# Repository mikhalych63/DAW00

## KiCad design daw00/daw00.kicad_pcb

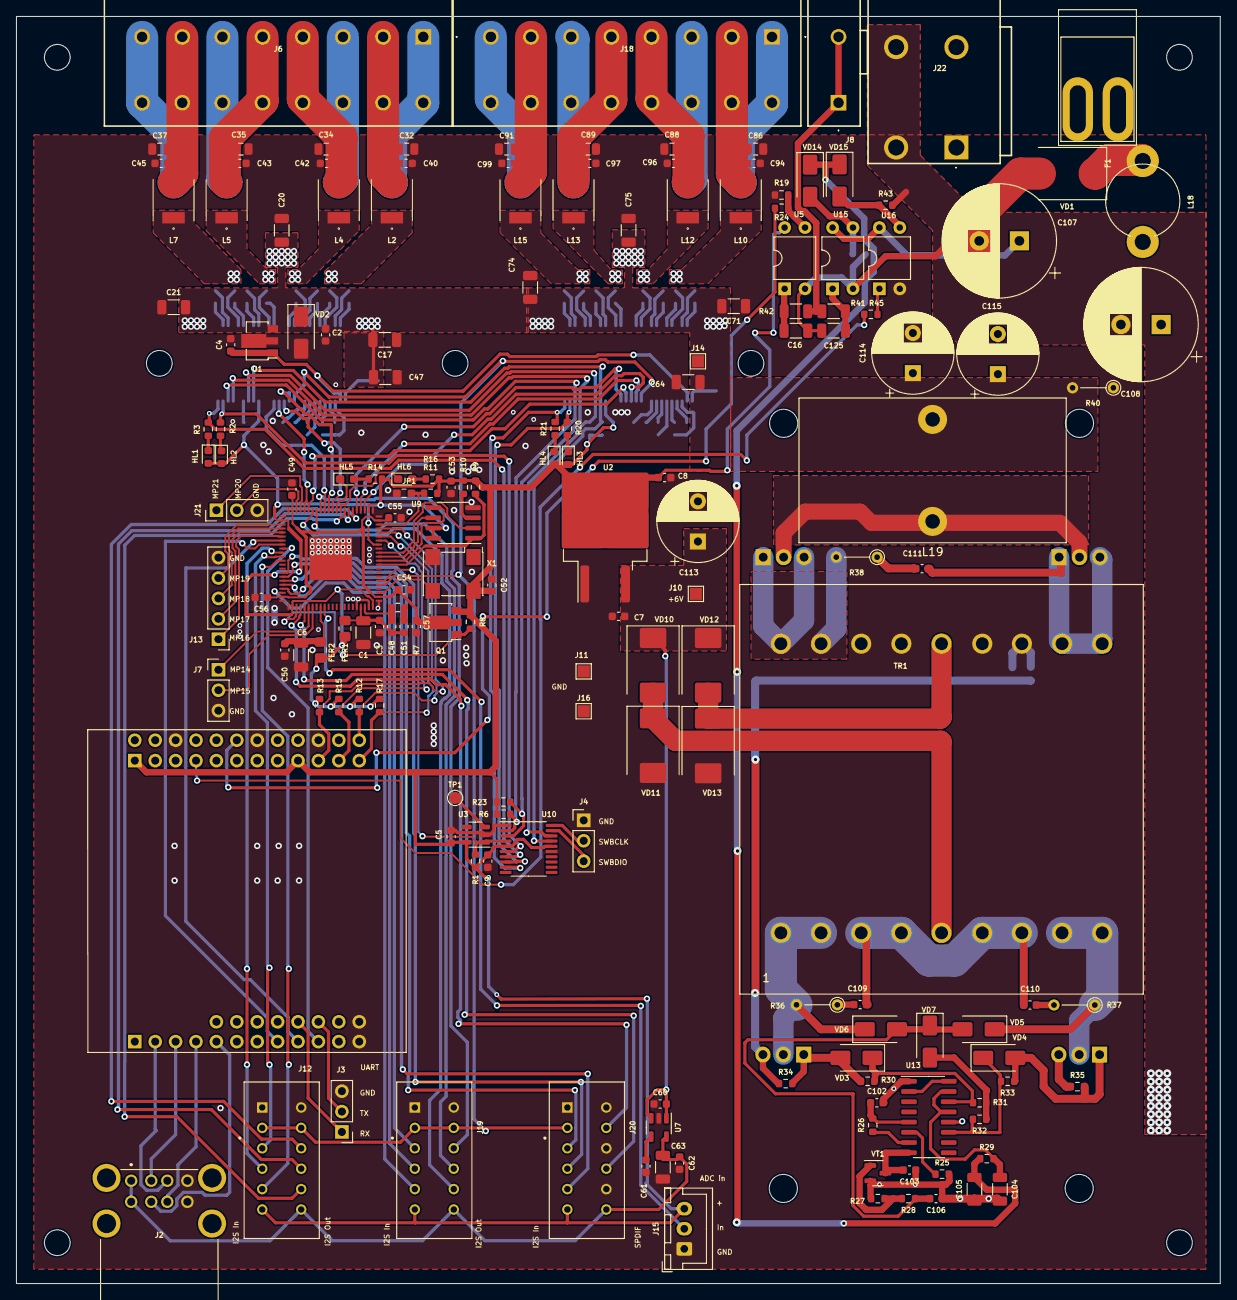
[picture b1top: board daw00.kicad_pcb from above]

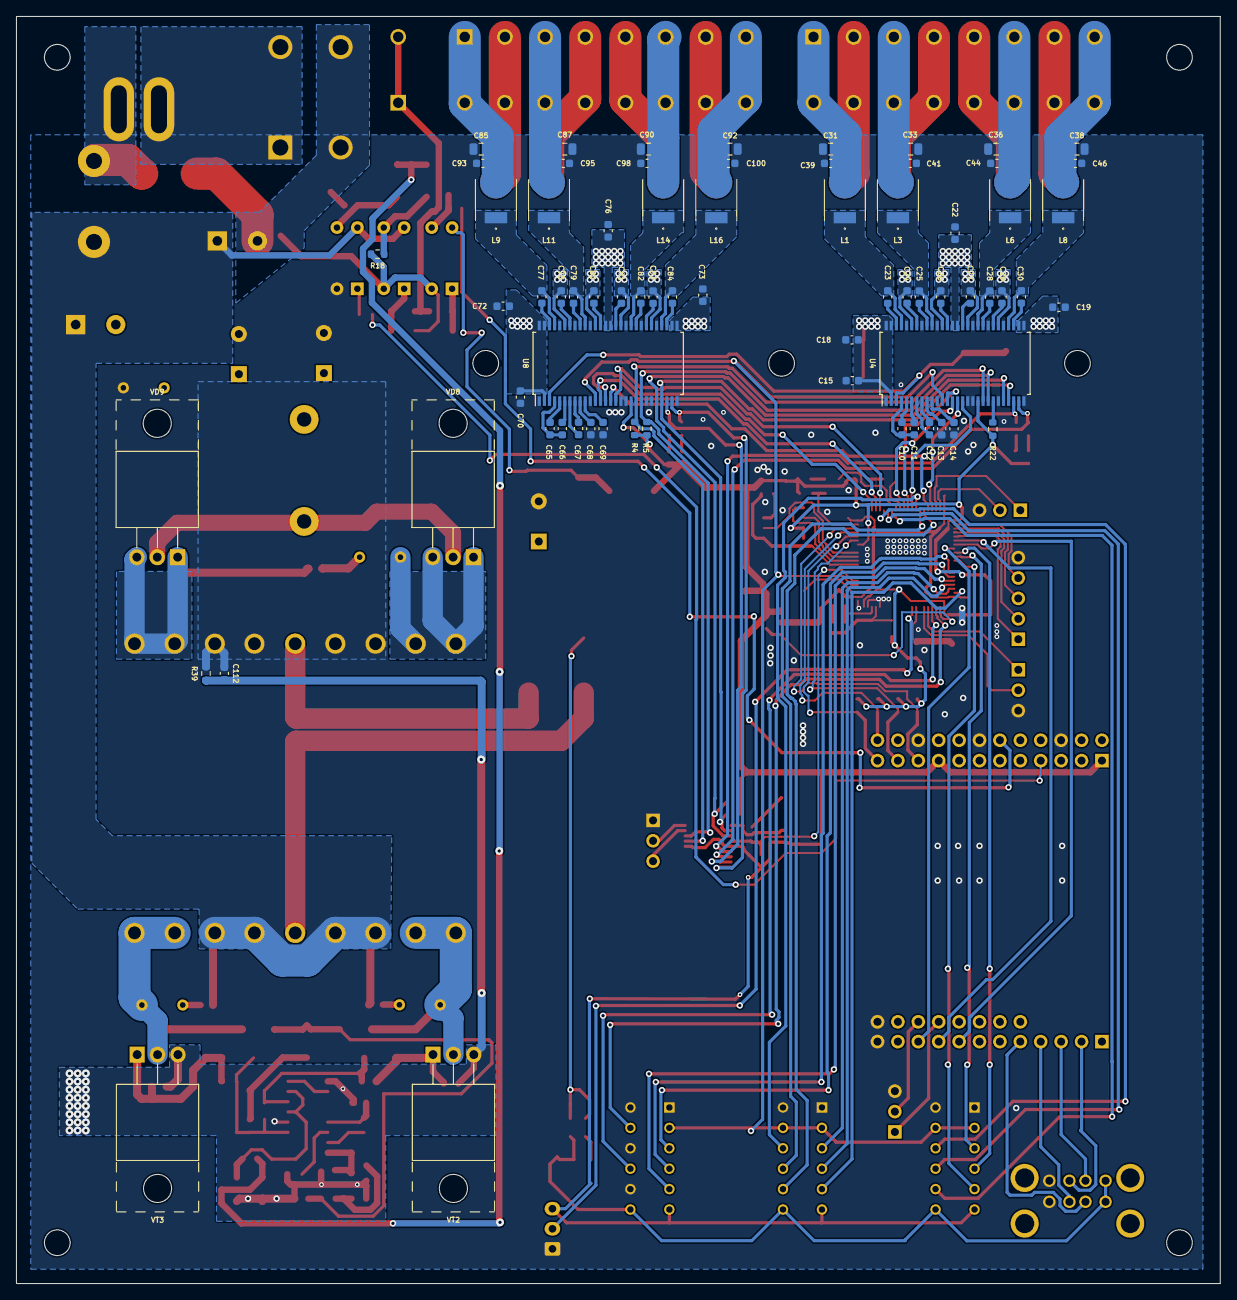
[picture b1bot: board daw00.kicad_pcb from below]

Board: 2 copper layers, 149.9 x 157.7 mm, 239 parts (70 on the bottom side), 188 nets.

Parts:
C1, C6, C16, C105, C125: CAP_10u0_50V_X7R_1206; C_1206_3216Metric
C2, C7: 0,33uF; C_0603_1608Metric
C3, C5, C50, C53, C54, C55, C56, C57, C112: CAP_100n_50V_X7R_0603; C_0603_1608Metric
C4, C8, C9, C15, C18, C19, C22, C60, C62, C70, C72, C73, C76: 100n; C_0603_1608Metric
C10, C11, C12, C13, C14, C23, C24, C25, C26, C27, C28, C29, C30, C65, C66, C67, C68, C69, C77, C78, C79, C80, C81, C82, C83, C84: 1,0uF; C_0603_1608Metric
C17, C20, C21, C47, C63, C64, C71, C74, C75: 10,0uF; C_1206_3216Metric
C31, C32, C33, C34, C35, C36, C37, C38, C85, C86, C87, C88, C89, C90, C91, C92: 1.0uF; C_0805_2012Metric
C39, C40, C41, C42, C43, C44, C45, C46, C61, C93, C94, C95, C96, C97, C98, C99, C100: 10n; C_0603_1608Metric
C48: CAP_150p_50V_C0G_0603; C_0603_1608Metric
C49, C103, C106: CAP_10n_50V_X7R_0603; C_0603_1608Metric
C51: CAP_5n6_50V_X7R_0603; C_0603_1608Metric
C52: CAP_10n_25V_X7R_0603; C_0603_1608Metric
C102, C111: CAP_1n_50V_X7R_0603; C_0603_1608Metric
C104: CAP_2u2_50V_X7R_1206; C_1206_3216Metric
C107, C108: 2200μ; CP_Radial_D14.0mm_P5.00mm
C109, C110: CAP_22n_50V_X7R_0603; C_0603_1608Metric
C113, C114, C115: 330μ; CP_Radial_D10.0mm_P5.00mm
F1: Fuse; Fuse_Blade_vertical
FER1, FER2: BLM21AG102SN1D; R_0805_2012Metric_Pad1.20x1.40mm_HandSolder
HL1, HL4: LED_SMD_0603_YELLOW; LED_0603_1608Metric
HL2, HL3: LED_SMD_0603_RED; LED_0603_1608Metric
HL5, HL6: LED_SMD_0603_BLUE; LED_0603_1608Metric_Pad1.05x0.95mm_HandSolder
J2: USB_A_Stacked; USB_A_STACKED
J3: UART; PinHeader_1x03_P2.54mm_Vertical
J4: SWD; PinHeader_1x03_P2.54mm_Vertical
J6, J18: DEGSON 2604 8x5; DEGSON_8x5
J7, J21: Conn_01x02_Male; PinHeader_1x03_P2.54mm_Vertical
J8: DEGSON 2604 1x5; DEGSON_1x5
J10: +6V; TestPoint_Pad_1.5x1.5mm
J11, J16: GND; TestPoint_Pad_1.5x1.5mm
J12, J19, J20: Conn_edge_2x6_2.54_Male; 2x6
J13: Conn_01x04_Male; PinHeader_1x05_P2.54mm_Vertical
J14: +24V; TestPoint_Pad_1.5x1.5mm
J15: Volume; JST_XH_B3B-XH-A_1x03_P2.50mm_Vertical
J22: KF206-7.5-2P; DEGSON_2x7.5
JP1: CON_JUMPER; R_0603_1608Metric_Pad0.98x0.95mm_HandSolder
L1, L2, L3, L4, L5, L6, L7, L8, L9, L10, L11, L12, L13, L14, L15, L16: 3.3uH; SPM5010-5020
L18: 5μ; L_Axial_L26.0mm_D9.0mm_P5.08mm_Vertical
L19: 25μ; L_Toroid_Vertical_L33.0mm_W17.8mm_P12.70mm_Pulse_KM-5
Q1: 2STF2360; SOT-89-3
R1, R6, R23: 10K; R_0603_1608Metric
R2, R3, R20, R21: 1K; R_0603_1608Metric
R4, R5, R22: 4k7; R_0603_1608Metric
R7: RES_4K3_1%_0.125W_Thick_0603; R_0603_1608Metric
R8: RES_1K0_1%_0.125W_Thick_0603; R_0603_1608Metric
R9, R10, R11, R12, R13, R15, R17: RES_10K0_1%_0.125W_Thick_0603; R_0603_1608Metric
R14, R16: RES_51R0_1%_0.125W_Thick_0603; R_0603_1608Metric
R18, R43: 4.7k; R_0603_1608Metric
R19: 10k; R_0603_1608Metric
R24, R31, R32, R34, R35, R39, R45: 1k; R_0603_1608Metric
R25: 15k; R_0603_1608Metric
R26: 150; R_0603_1608Metric
R27: 3k; R_0603_1608Metric
R28: 3,6k; R_0603_1608Metric
R29, R30, R33: 10; R_0603_1608Metric
R36, R37: 4.7; R_Axial_DIN0204_L3.6mm_D1.6mm_P5.08mm_Vertical
R38: 100; R_Axial_DIN0204_L3.6mm_D1.6mm_P5.08mm_Vertical
R40: 1.5k; R_Axial_DIN0204_L3.6mm_D1.6mm_P5.08mm_Vertical
R41, R42: 1.2k; R_1206_3216Metric
TP1: Reset; TestPoint_Pad_D1.5mm
TR1: TRANSF10; Transformer_ETD44_Horizontal
U1: L78L18_SOT89; SOT-89-3
U2: LD1086D2T33TR; TO-263-2
U3: TPS3828-33DBVT; SOT-23-5
U4, U8: TAS6424QDKQRQ1; SSOP-56_7.5x18.5mm_P0.635mm
U5, U15, U16: TLP627; DIP-4_W7.62mm
U6: ADAU1467WBCPZ300RL; LFCSP-88-1EP_10x10mm_P0.5mm_EP6.15x6.15mm
U7: LP2985-5.0; SOT-23-5
U9: 25AA1024-I/SM; SOIC-8_3.9x4.9mm_P1.27mm
U10: STM32F030F4Px; TSSOP-20_4.4x6.5mm_P0.65mm
U12: Nanopi NEO Air; Nanopi NEO
U13: SG3525; SOIC-16_3.9x9.9mm_P1.27mm
VD1, VD10, VD11, VD12, VD13: SS56; D_SMC
VD2: ES1D; D_SMA
VD3, VD4, VD5, VD14, VD15: 1N5819; D_SMA
VD6, VD7: 1N414E; D_SMA
VD8, VD9: MBR20100CT; TO-220-3_Horizontal_TabUp
VT1: BC846; SOT-23
VT2, VT3: IRF3205; TO-220-3_Horizontal_TabUp
X1: SG-8002CA 24.5760M-PCBL3; Oscillator_SMD_SeikoEpson_SG8002CA-4Pin_7.0x5.0mm

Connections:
+3V3: C5.2, C8.1, C9.2, C52.1, C53.1, FER1.2, FER2.2, HL1.2 (A), HL2.2 (A), HL3.2 (A), HL4.2 (A), J12.11, J15.3, J19.11, J20.11, Q1.3 (E), R1.1, R4.1, R5.1, R6.1, R8.2, R9.1, R10.1, R11.1, R12.1, R13.1, R14.1, R15.1, R16.1, R17.1, R22.2, R23.1, U2.2 (OUT), U3.5 (VDD), U4.19 (VDD), U5.4, U6.2 (IOVDD), U6.22 (IOVDD), U6.37 (IOVDD), U6.46 (IOVDD), U6.68 (IOVDD), U8.19 (VDD), U9.7 (~HOLD), U9.8 (VCC), U10.5 (VDDA), U10.16 (VDD), U12.1 (VDD_3.3V), U12.17 (VDD_3.3V), X1.4 (Vcc)
+5V: C62.2, C63.1, J2.1 (VBUS1), J2.5 (VBUS2), J12.12, J19.12, J20.12, U7.5 (VOUT)
+6V: C7.1, C60.2, C113.1, J10.1, U2.3 (IN), U7.1 (VIN), U7.3 (ON/~OFF), VD10.1 (K), VD12.1 (K)
+BATT: F1.1, J22.1
/Amplifier/AUXADC0: J15.2, U6.10 (AUXADC0)
/Amplifier/BCLKIN1: J12.7, U6.76 (BCLK_IN1)
/Amplifier/BCLKIN2: J20.7, U6.81 (BCLK_IN2)
/Amplifier/BCLKIN3: J19.7, U6.84 (BCLK_IN3)
/Amplifier/BCLKOUT0: U6.48 (BCLK_OUT0), U8.13 (SCLK)
/Amplifier/BCLKOUT1: J12.8, U6.51 (BCLK_OUT1)
/Amplifier/BCLKOUT2: U4.13 (SCLK), U6.56 (BCLK_OUT2)
/Amplifier/BCLKOUT3: J19.8, U6.59 (BCLK_OUT3)
/Amplifier/LRCKIN1: J12.5, U6.77 (LRCLK_IN1/MP11)
/Amplifier/LRCKIN2: J20.5, U6.82 (LRCLK_IN2/MP12)
/Amplifier/LRCKIN3: J19.5, U6.85 (LRCLK_IN3/MP13)
/Amplifier/LRCKOUT1: J12.6, U6.50 (LRCLK_OUT1/MP5)
/Amplifier/LRCKOUT3: J19.6, U6.58 (LRCLK_OUT3/MP9)
/Amplifier/LRCLKOUT0: U6.47 (LRCLK_OUT0/MP4), U8.14 (FSYNC)
/Amplifier/LRCLKOUT2: U4.14 (FSYNC), U6.55 (LRCLK_OUT2/MP8)
/Amplifier/SDATAIN1: J12.9, U6.78 (SDATA_IN1)
/Amplifier/SDATAIN2: J20.9, U6.83 (SDATA_IN2)
/Amplifier/SDATAIN3: J19.9, U6.86 (SDATA_IN3)
/Amplifier/SDATAOUT0: U6.49 (SDATA_OUT0), U8.16 (SDIN2)
/Amplifier/SDATAOUT1: J12.10, U6.52 (SDATA_OUT1)
/Amplifier/SDATAOUT1+: U6.61 (SDATAIO7/MP23), U8.15 (SDIN1)
/Amplifier/SDATAOUT2: U4.16 (SDIN2), U6.57 (SDATA_OUT2)
/Amplifier/SDATAOUT3: J19.10, U6.60 (SDATA_OUT3)
/Amplifier/SDATAOUT3+: U4.15 (SDIN1), U6.62 (SDATAIO6/MP22)
/Amplifier/SPDIFIN: J20.4, U6.4 (SPDIFIN)
/Amplifier/SPDIFOUT: J20.8, U6.5 (SPDIFOUT)
/Computer/SBWTCK: J4.2, U10.20 (PA14)
/Computer/SBWTDIO: J4.3, U10.19 (PA13)
ACC: J8.1, R41.2, R42.2
ACC_IN: R24.2, U12.12 (GPIO_A6)
BCLKIN0: U6.73 (BCLK_IN0), U12.39 (I2S0_BCK)
FAULT0: R21.2, U8.27 (FAULT), U10.9 (PA3)
FAULT1: R3.2, U4.27 (FAULT), U10.7 (PA1)
GND: C1.2, C2.2, C3.2, C4.2, C5.1, C6.2, C7.2, C8.2, C9.1, C13.2, C14.2, C15.1, C17.1, C18.1, C19.1, C20.2, C21.1, C22.2, C31.1, C32.2, C33.1, C34.2, C35.1, C36.2, C37.1, C38.2, C39.1, C40.2, C41.1, C42.2, C43.1, C44.2, C45.1, C46.2, C47.1, C49.2, C50.2, C52.2, C53.2, C54.2, C55.2, C56.2, C57.2, C60.1, C61.1, C62.1, C63.2, C64.1, C68.2, C69.2, C70.1, C71.1, C72.1, C73.1, C74.2, C75.1, C76.2, C85.1, C86.2, C87.1, C88.2, C89.1, C90.2, C91.1, C92.2, C93.1, C94.2, C95.1, C96.2, C97.1, C98.2, C99.1, C100.2, C112.1, C113.2, C114.2, C115.2, J2.4 (GND1), J2.8 (GND2), J3.3, J4.1, J7.3, J11.1, J12.1, J12.2, J13.5, J15.1, J16.1, J19.1, J19.2, J20.1, J20.2, J20.6, J20.10, J21.3, JP1.2, R19.2, R39.2, R40.1, TR1.6, TR1.7, U1.2 (GND), U2.1 (ADJ/GND), U3.2 (GND), U4.1 (GND), U4.11 (GND), U4.17 (GND), U4.18 (GND), U4.23 (I2C_ADDR1), U4.28 (GND), U4.33 (GND), U4.36 (GND), U4.39 (GND), U4.46 (GND), U4.49 (GND), U4.52 (GND), U6.1 (DGND), U6.8 (AGND), U6.18 (PGND), U6.21 (DGND), U6.23 (DGND), U6.29 (DGND), U6.36 (DGND), U6.44 (DGND), U6.45 (DGND), U6.66 (DGND), U6.67 (DGND), U6.88 (DGND), U6.89 (GND), U7.2 (GND), U8.1 (GND), U8.11 (GND), U8.17 (GND), U8.18 (GND), U8.22 (I2C_ADDR0), U8.23 (I2C_ADDR1), U8.28 (GND), U8.33 (GND), U8.36 (GND), U8.39 (GND), U8.46 (GND), U8.49 (GND), U8.52 (GND), U9.4 (VSS), U10.1 (BOOT0), U10.15 (VSS), U12.6 (GND), U12.14 (GND), U12.20 (GND), U12.42 (GND), U12.50 (GND), U16.2, VD2.2 (A), VD11.2 (A), VD13.2 (A), X1.2 (GND)
GNDPWR: C16.2, C102.2, C103.1, C104.2, C105.2, C106.1, C107.2, C108.2, C112.2, C125.2, J22.2, R18.2, R25.2, R27.1, R34.1, R35.1, R39.1, R43.2, U5.2, U13.1 (INV), U13.12 (GND), U15.2, VD1.2 (A), VT1.2 (E), VT2.3 (S), VT3.3 (S)
LRCKIN0: U6.74 (LRCLK_IN0/MP10), U12.38 (I2S0_LRCK)
MCLK: J12.3, J12.4, J19.3, J19.4, J20.3, U4.12 (MCLK), U6.27 (CLKOUT), U8.12 (MCLK)
MISO: R15.2, U6.38 (MISO/SDA), U12.21 (SPI0_MISO)
MOSI: R13.2, U6.41 (SS/ADDR0), U12.19 (SPI0_MOSI)
Mute: R23.2, U4.24 (MUTE), U8.24 (MUTE), U10.3 (PF1)
unnamed: C13.1, U4.9 (GVDD)
unnamed: C14.1, U4.10 (GVDD)
unnamed: C16.1, R42.1, U5.1
unnamed: C51.2, R7.2
unnamed: C68.1, U8.9 (GVDD)
unnamed: C69.1, U8.10 (GVDD)
unnamed: C107.1, C108.1, C109.2, C110.1, L18.2, TR1.2, TR1.3, U15.4, U16.4
unnamed: C109.1, R36.1
unnamed: C110.2, R37.2
unnamed: C111.1, R38.1
unnamed: C125.1, R41.1, U15.1
unnamed: HL1.1 (K), R3.1
unnamed: HL2.1 (K), R2.2
unnamed: HL3.1 (K), R20.2
unnamed: HL4.1 (K), R21.1
unnamed: HL5.2 (A), R14.2
unnamed: HL5.1 (K), U6.54 (MP7)
unnamed: HL6.2 (A), R16.2
unnamed: HL6.1 (K), U6.53 (MP6)
unnamed: J2.3 (D1+), U12.32 (USB_DP1)
unnamed: J2.2 (D1-), U12.33 (USB_DM1)
unnamed: J2.7 (D2+), U12.34 (USB_DP2)
unnamed: J2.6 (D2-), U12.35 (USB_DM2)
unnamed: J3.1, U12.47 (UART0RX)
unnamed: J3.2, U12.48 (UART0TX)
unnamed: C31.2, C39.2, J6.1, L1.2
unnamed: C32.1, C40.1, J6.2, L2.2
unnamed: C33.2, C41.2, J6.3, L3.2
unnamed: C34.1, C42.1, J6.4, L4.2
unnamed: C35.2, C43.2, J6.5, L5.2
unnamed: C36.1, C44.1, J6.6, L6.2
unnamed: C37.2, C45.2, J6.7, L7.2
unnamed: C38.1, C46.1, J6.8, L8.2
unnamed: J7.1, U6.6 (MP14)
unnamed: J7.2, U6.7 (MP15)
unnamed: J13.1, U6.72 (SDATAIO0/MP16)
unnamed: J13.2, U6.71 (SDATAIO1/MP17)
unnamed: J13.3, U6.70 (SDATAIO2/MP18)
unnamed: J13.4, U6.69 (SDATAIO3/MP19)
unnamed: C85.2, C93.2, J18.1, L9.2
unnamed: C86.1, C94.1, J18.2, L10.2
unnamed: C87.2, C95.2, J18.3, L11.2
unnamed: C88.1, C96.1, J18.4, L12.2
unnamed: C89.2, C97.2, J18.5, L13.2
unnamed: C90.1, C98.1, J18.6, L14.2
unnamed: C91.2, C99.2, J18.7, L15.2
unnamed: C92.1, C100.1, J18.8, L16.2
unnamed: J21.1, U6.63 (SDATAIO5/MP21)
unnamed: J21.2, U6.64 (SDATAIO4/MP20)
unnamed: Q1.1 (B), R8.1, U6.3 (VDRIVE)
unnamed: R19.1, R24.1, U5.3
unnamed: R45.2, U16.1
unnamed: TP1.1, U3.3 (~MR)
unnamed: C10.2, C11.2, U4.4 (AREF)
unnamed: C12.1, U4.8 (AVDD)
unnamed: C12.2, U4.7 (AVSS)
unnamed: C29.2, U4.35 (BST+1P)
unnamed: C30.1, U4.31 (BST_1M)
unnamed: C28.1, U4.37 (BST_2M)
unnamed: C27.2, U4.41 (BST_2P)
unnamed: C26.1, U4.44 (BST_3M)
unnamed: C25.2, U4.48 (BST_3P)
unnamed: C24.1, U4.50 (BST_4M)
unnamed: C23.2, U4.54 (BST_4P)
unnamed: R22.1, U4.22 (I2C_ADDR0)
unnamed: C30.2, L8.1, U4.32 (OUT_1M)
unnamed: C29.1, L7.1, U4.34 (OUT_1P)
unnamed: C28.2, L6.1, U4.38 (OUT_2M)
unnamed: C27.1, L5.1, U4.40 (OUT_2P)
unnamed: C26.2, L4.1, U4.45 (OUT_3M)
unnamed: C25.1, L3.1, U4.47 (OUT_3P)
unnamed: C24.2, L2.1, U4.51 (OUT_4M)
unnamed: C23.1, L1.1, U4.53 (OUT_4P)
unnamed: C11.1, U4.6 (VCOM)
unnamed: C10.1, U4.5 (VREG)
unnamed: C6.1, C50.1, FER2.1, U6.9 (AVDD)
unnamed: U6.33 (MOSI_M/MP1), U9.5 (SI)
unnamed: C48.2, R7.1, U6.20 (PLLFILT)
unnamed: C1.1, C3.1, C48.1, C51.1, FER1.1, U6.19 (PVDD)
unnamed: U6.34 (SCL_M/SCLK_M/MP2), U9.6 (SCK)
unnamed: U6.35 (SDA_M/MISO_M/MP3), U9.2 (SO)
unnamed: JP1.1, R11.2, U6.42 (SELFBOOT)
unnamed: R9.2, U6.32 (SS_M/MP0), U9.1 (~CS)
unnamed: U6.25 (XTALIN/MCLK), X1.3 (OUT)
unnamed: C61.2, U7.4 (BP)
unnamed: C65.2, C66.2, U8.4 (AREF)
unnamed: C67.1, U8.8 (AVDD)
unnamed: C67.2, U8.7 (AVSS)
unnamed: C83.2, U8.35 (BST+1P)
unnamed: C84.1, U8.31 (BST_1M)
unnamed: C82.1, U8.37 (BST_2M)
unnamed: C81.2, U8.41 (BST_2P)
unnamed: C80.1, U8.44 (BST_3M)
unnamed: C79.2, U8.48 (BST_3P)
unnamed: C78.1, U8.50 (BST_4M)
unnamed: C77.2, U8.54 (BST_4P)
unnamed: C84.2, L16.1, U8.32 (OUT_1M)
unnamed: C83.1, L15.1, U8.34 (OUT_1P)
unnamed: C82.2, L14.1, U8.38 (OUT_2M)
unnamed: C81.1, L13.1, U8.40 (OUT_2P)
unnamed: C80.2, L12.1, U8.45 (OUT_3M)
unnamed: C79.1, L11.1, U8.47 (OUT_3P)
unnamed: C78.2, L10.1, U8.51 (OUT_4M)
unnamed: C77.1, L9.1, U8.53 (OUT_4P)
unnamed: C66.1, U8.6 (VCOM)
unnamed: C65.1, U8.5 (VREG)
unnamed: R10.2, U9.3 (~WP)
unnamed: C102.1, R26.2, U13.5 (CT)
unnamed: R26.1, U13.7 (DISCH)
unnamed: U13.2 (NI), U13.16 (REF)
unnamed: R32.2, R33.2, U13.11 (OUTA), VD4.1 (K)
unnamed: R30.2, R31.2, U13.14 (OUTB), VD3.1 (K)
unnamed: R25.1, U13.6 (RT)
unnamed: C103.2, U13.8 (SS), VT1.3 (C)
unnamed: C104.1, R29.2, U13.13 (VC), U13.15 (VIN)
unnamed: F1.2, L18.1, VD1.1 (K)
unnamed: R30.1, R34.2, VD3.2 (A), VT2.1 (G)
unnamed: R33.1, R35.2, VD4.2 (A), VT3.1 (G)
unnamed: R31.1, R32.1, VD5.2 (A)
unnamed: C106.2, R28.1, VD5.1 (K), VD6.2 (A), VD7.2 (A)
unnamed: R36.2, TR1.1, VD6.1 (K), VT2.2 (D)
unnamed: R37.1, TR1.4, VD7.1 (K), VT3.2 (D)
unnamed: R38.2, TR1.8, VD8.1 (A1), VD8.3 (A2)
unnamed: L19.1, VD8.2 (A), VD9.2 (A)
unnamed: C111.2, TR1.5, VD9.1 (A1), VD9.3 (A2)
unnamed: TR1.10, VD10.2 (A), VD11.1 (K)
unnamed: TR1.9, VD12.2 (A), VD13.1 (K)
unnamed: R18.1, U15.3, VD14.2 (A)
unnamed: C105.1, R29.1, VD14.1 (K), VD15.1 (K)
unnamed: R43.1, U16.3, VD15.2 (A)
unnamed: R27.2, R28.2, VT1.1 (B)
PVDD: C2.1, C15.2, C17.2, C18.2, C19.2, C20.1, C21.2, C22.1, C47.2, C64.2, C70.2, C71.2, C72.2, C73.2, C74.1, C75.2, C76.1, C114.1, C115.1, J14.1, L19.2, R40.2, U1.3 (IN), U4.2 (PVDD), U4.29 (PVDD), U4.30 (PVDD), U4.42 (PVDD), U4.43 (PVDD), U4.55 (PVDD), U4.56 (PVDD), U8.2 (PVDD), U8.29 (PVDD), U8.30 (PVDD), U8.42 (PVDD), U8.43 (PVDD), U8.55 (PVDD), U8.56 (PVDD), VD2.1 (K)
REMOTE: R45.1, U12.7 (GPIO_G11)
RST: R1.2, U3.1 (~RESET), U6.28 (RESET), U10.4 (NRST)
SCL: R4.2, U4.20 (SCL), U8.20 (SCL), U10.17 (PA9)
SCL: R17.2, U6.39 (SCLK/SCL), U12.23 (SPI0_CLK)
SDA: R5.2, U4.21 (SDA), U8.21 (SDA), U10.18 (PA10)
SDATAIN0: U6.75 (SDATA_IN0), U12.40 (I2S0_SDOUT)
SS: R12.2, U6.40 (MOSI/ADDR1), U12.24 (SPI0_CS)
Standby: R6.2, U4.25 (STANDBY), U8.25 (STANDBY), U10.2 (PF0)
VBAT: C4.1, U1.1 (OUT), U4.3 (VBAT), U8.3 (VBAT)
VPP: C49.1, C54.1, C55.1, C56.1, C57.1, Q1.2 (C), U6.24 (DVDD), U6.43 (DVDD), U6.65 (DVDD), U6.87 (DVDD)
WARN0: R20.1, U8.26 (WARN), U10.8 (PA2)
WARN1: R2.1, U4.26 (WARN), U10.6 (PA0)

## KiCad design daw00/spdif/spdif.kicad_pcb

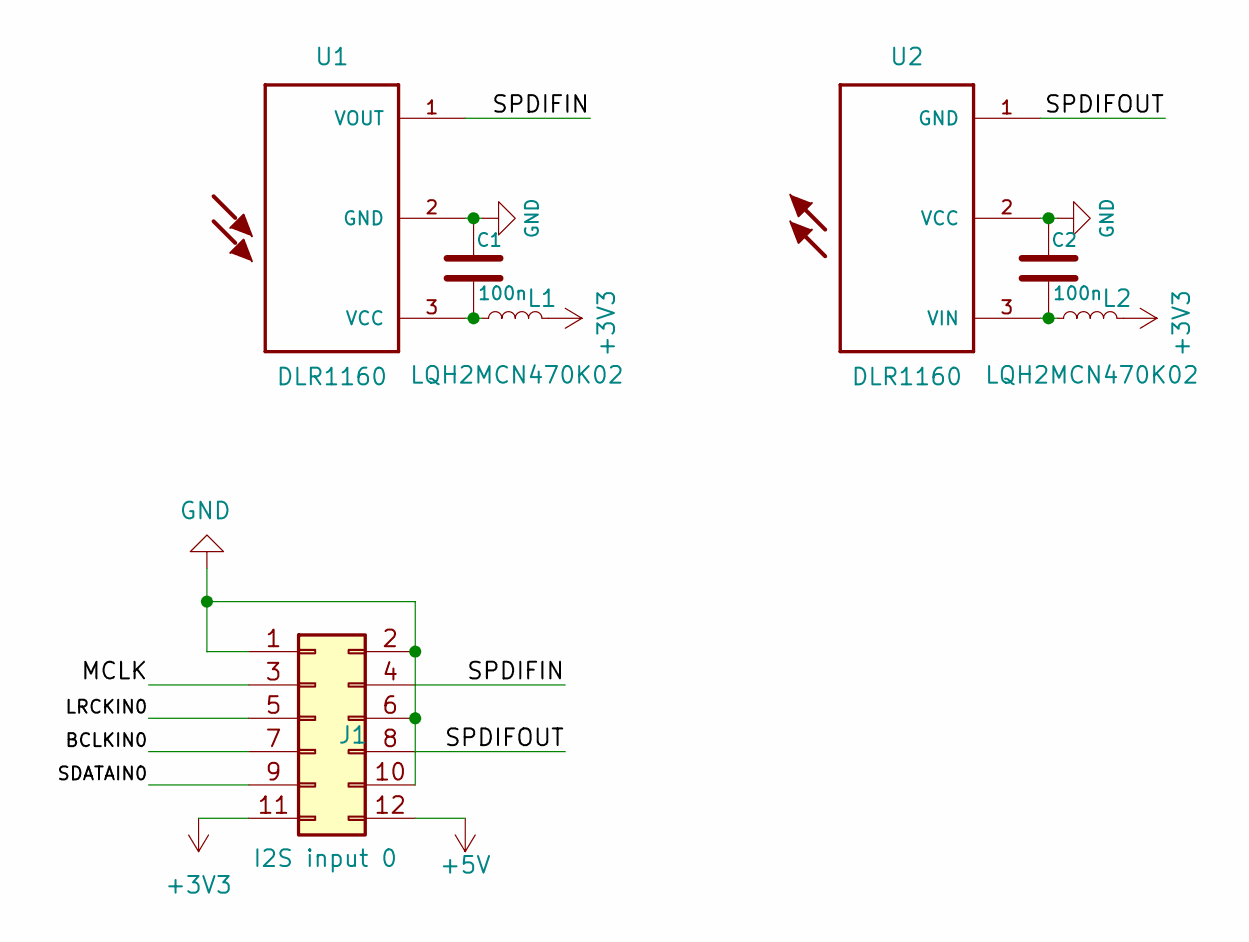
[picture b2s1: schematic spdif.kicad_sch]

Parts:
C1, C2: CAP_100n_25V_X7R_0603; C_0603_1608Metric
J1: Conn_01x06_Male; EDGE-2x6-2.54
L1, L2: LQH2MCN470K02; L_Murata_LQH2MCNxxxx02_2.0x1.6mm
U1, U2: DLR1160; Toslink

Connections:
+3V3: J1.11, L1.2, L2.2
+5V: J1.12
/BCLKIN0: J1.7
/LRCKIN0: J1.5
/MCLK: J1.3
/SDATAIN0: J1.9
/SPDIFIN: J1.4, U1.1 (VOUT)
/SPDIFOUT: J1.8, U2.1 (GND)
GND: C1.1, C2.1, J1.1, J1.2, J1.6, J1.10, U1.2 (GND), U1.NC1, U1.NC2, U2.2 (VCC), U2.NC1, U2.NC2
unnamed: C1.2, L1.1, U1.3 (VCC)
unnamed: C2.2, L2.1, U2.3 (VIN)

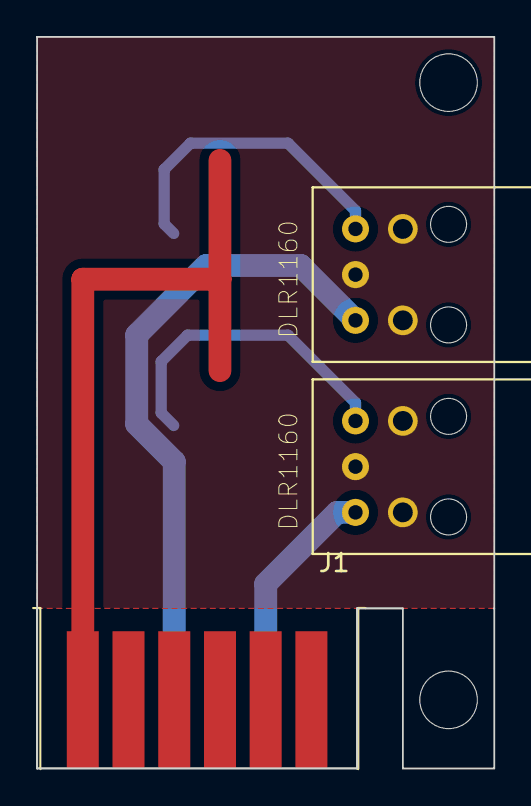
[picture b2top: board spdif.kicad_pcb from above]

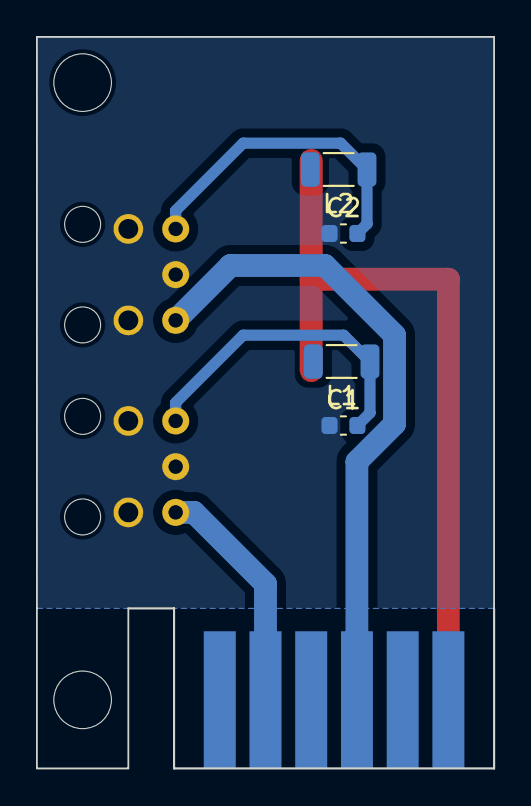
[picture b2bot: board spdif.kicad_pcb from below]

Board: 2 copper layers, 25.4 x 40.6 mm, 7 parts (4 on the bottom side), 6 nets.

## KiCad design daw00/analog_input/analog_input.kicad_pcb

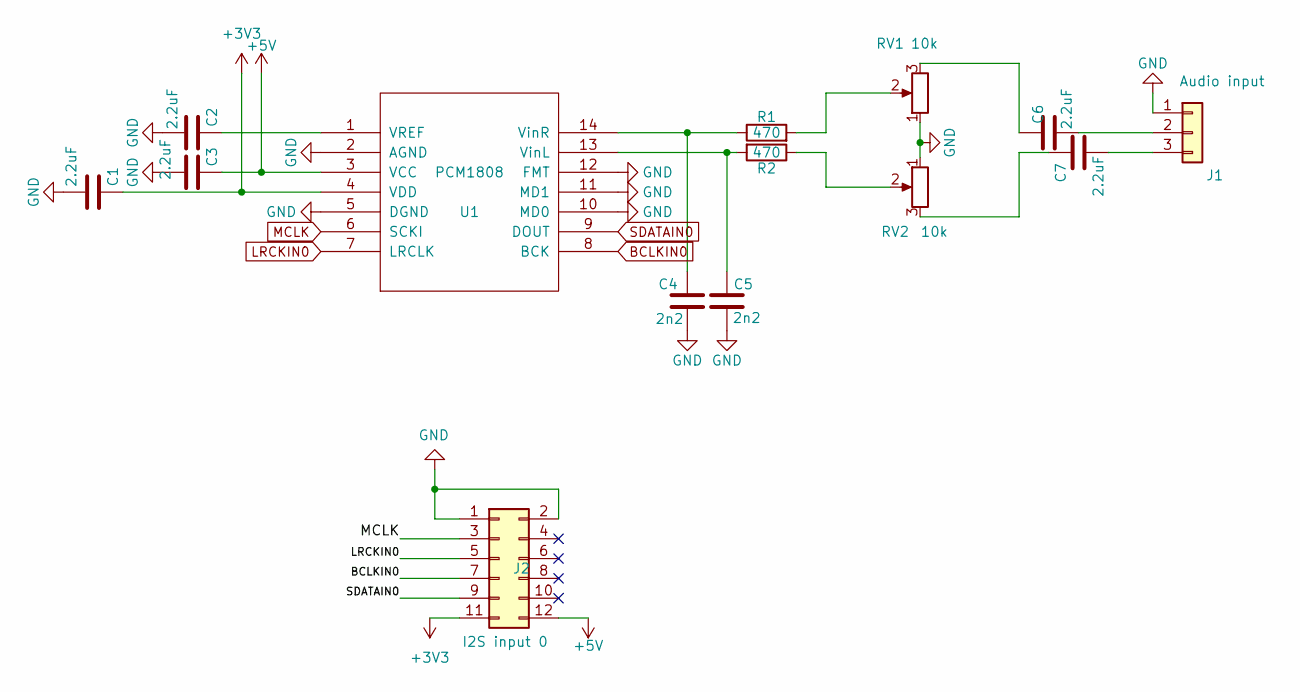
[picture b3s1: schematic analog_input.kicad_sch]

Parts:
C1, C2, C3, C6, C7: 2.2uF; C_0805_2012Metric
C4, C5: 2n2; C_0603_1608Metric
J1: Conn_01x03_Male; PJ313
J2: Conn_01x06_Male; EDGE-2x6-2.54
R1, R2: 470; R_0603_1608Metric
RV1, RV2: 10k; Potentiometer_Bourns_3266P_Horizontal
U1: PCM1808; TSSOP-14_4.4x5mm_P0.65mm

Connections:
+3V3: C1.1, J2.11, U1.4 (VDD)
+5V: C3.1, J2.12, U1.3 (VCC)
BCLKIN0: J2.7, U1.8 (BCK)
GND: C1.2, C2.2, C3.2, C4.1, C5.1, J1.1, J2.1, J2.2, RV1.1, RV2.1, U1.2 (AGND), U1.5 (DGND), U1.10 (MD0), U1.11 (MD1), U1.12 (FMT)
LRCKIN0: J2.5, U1.7 (LRCLK)
MCLK: J2.3, U1.6 (SCKI)
unnamed: C6.2, RV1.3
unnamed: C7.1, RV2.3
unnamed: C6.1, J1.2
unnamed: C7.2, J1.3
unnamed: R1.2, RV1.2
unnamed: R2.1, RV2.2
unnamed: C2.1, U1.1 (VREF)
unnamed: C5.2, R2.2, U1.13 (VinL)
unnamed: C4.2, R1.1, U1.14 (VinR)
SDATAIN0: J2.9, U1.9 (DOUT)

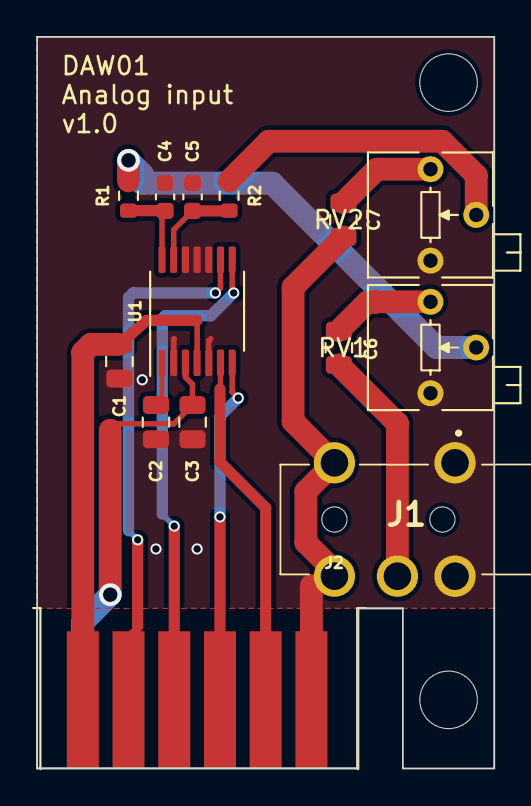
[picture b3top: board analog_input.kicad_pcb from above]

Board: 2 copper layers, 25.4 x 40.6 mm, 14 parts (0 on the bottom side), 16 nets.

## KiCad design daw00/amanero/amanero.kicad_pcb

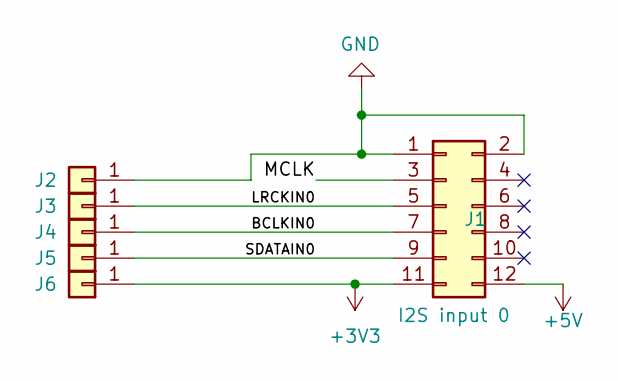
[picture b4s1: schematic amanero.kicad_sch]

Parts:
J1: Conn_01x06_Male; EDGE-2x6-2.54
J2, J3, J4, J5, J6: Conn_01x01; TestPoint_THTPad_1.0x1.0mm_Drill0.5mm

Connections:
+3V3: J1.11, J6.1
+5V: J1.12
/BCLKIN0: J1.7, J4.1
/LRCKIN0: J1.5, J3.1
/MCLK: J1.3
/SDATAIN0: J1.9, J5.1
GND: J1.1, J1.2, J2.1

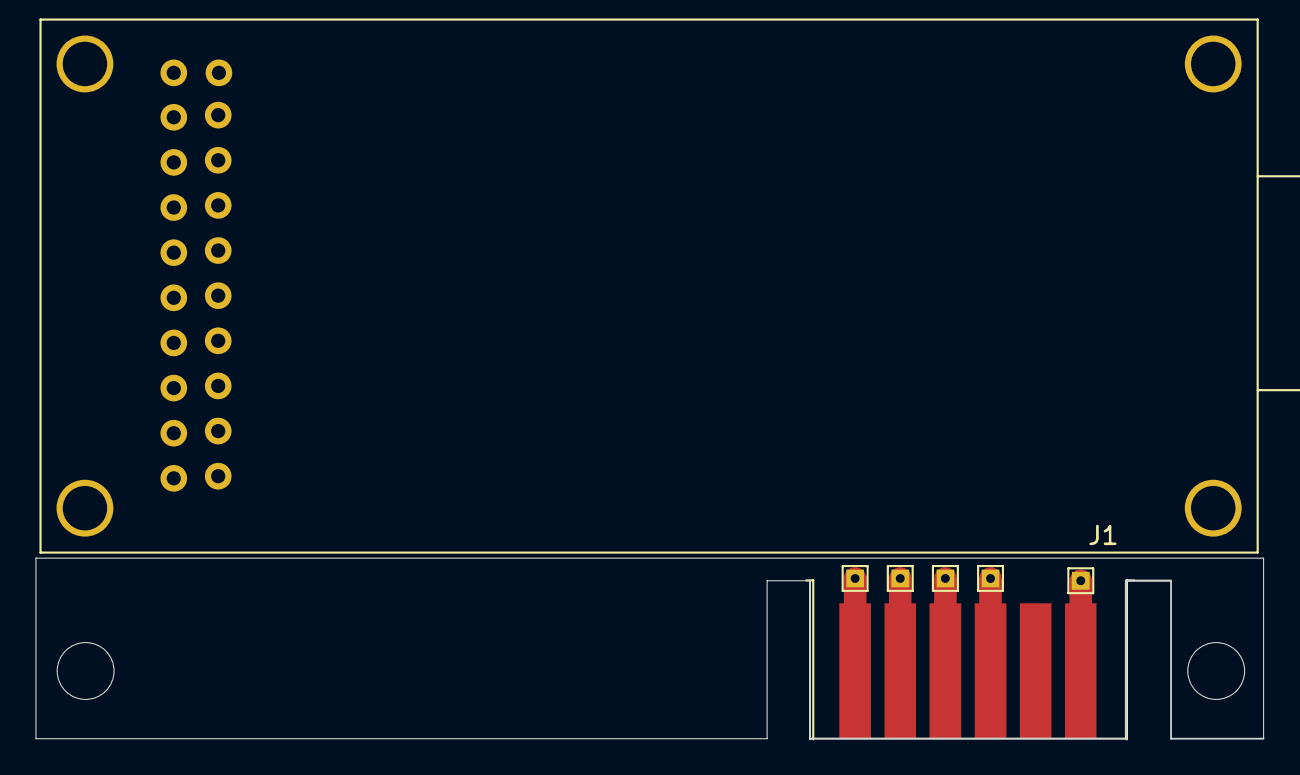
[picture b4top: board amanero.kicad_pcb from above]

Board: 2 copper layers, 69.1 x 10.2 mm, 6 parts (0 on the bottom side), 5 nets.

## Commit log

2023-10-23 Start
2024-01-30 Чтоб не потерялось
2024-02-14 Промежуточная
2024-02-16 next
2024-02-22 Почти все
2024-02-29 Основная плата все
2024-03-03 Добавил надписи
2024-03-20 Добавил корпус
